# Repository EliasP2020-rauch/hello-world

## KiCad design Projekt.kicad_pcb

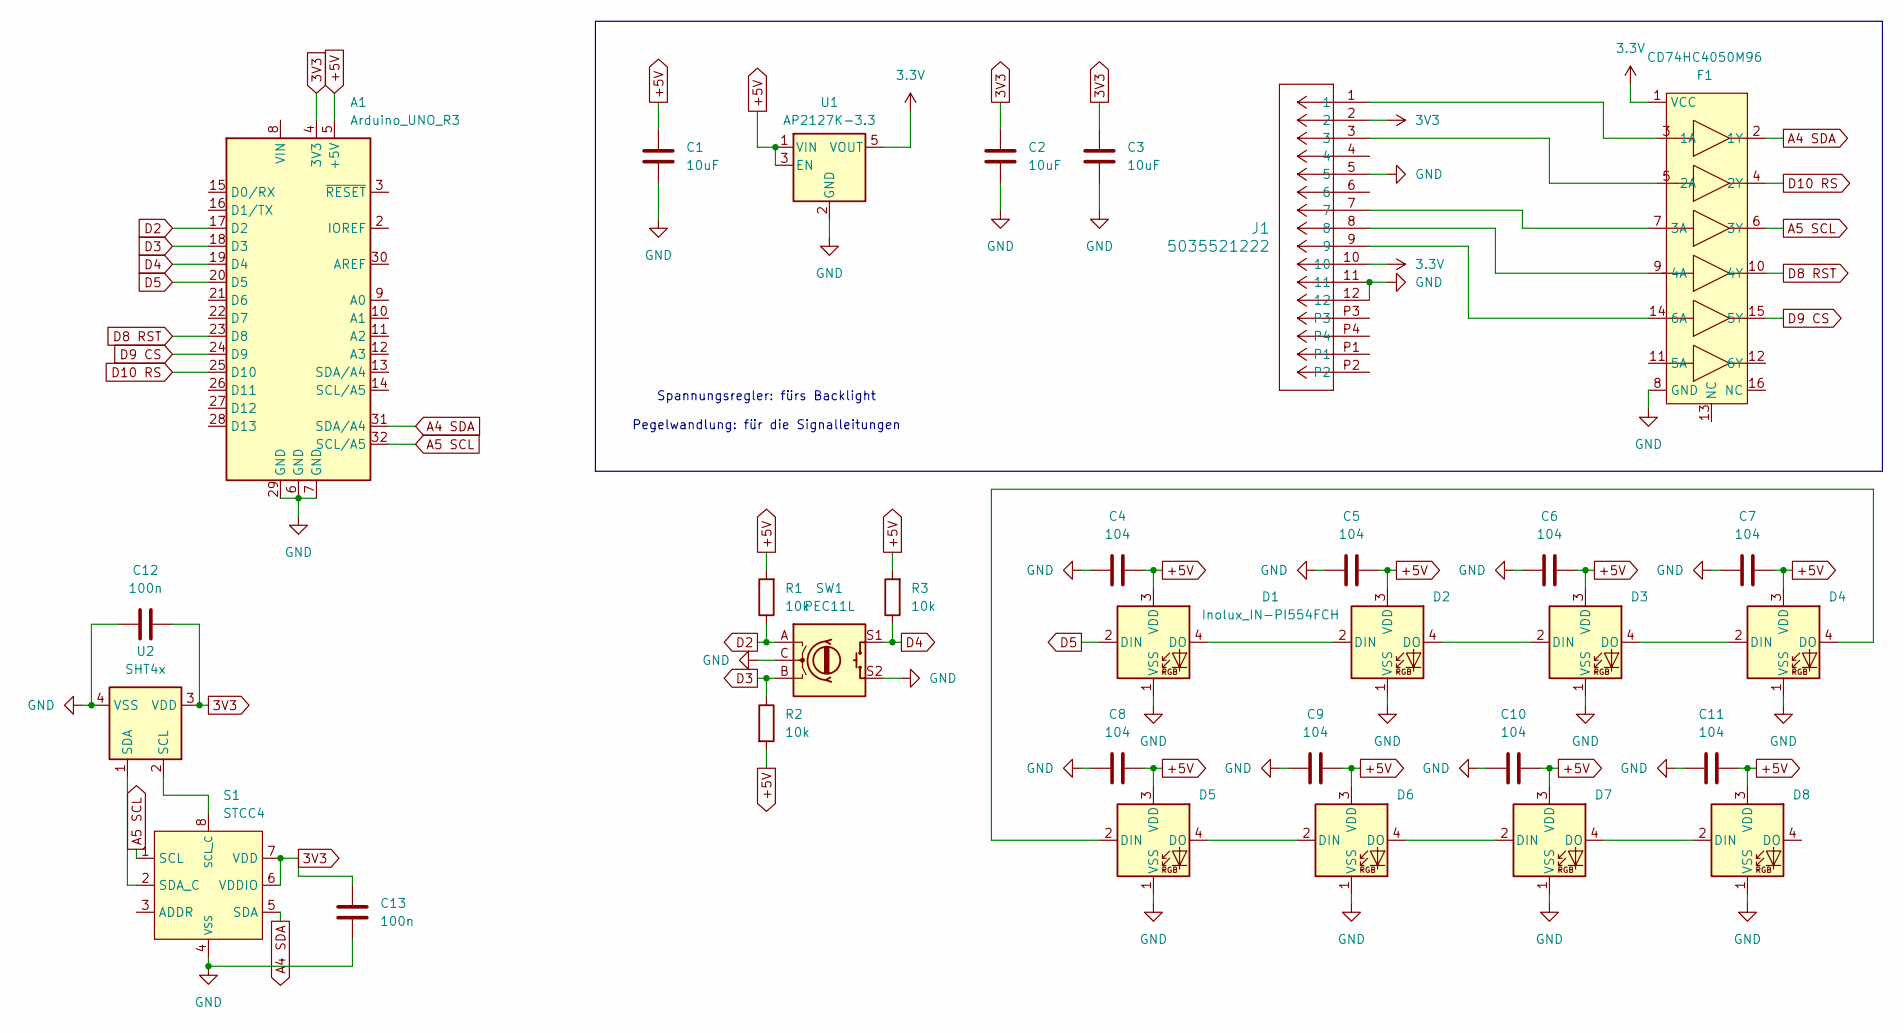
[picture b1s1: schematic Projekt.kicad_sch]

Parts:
A1: Arduino_UNO_R3
C1, C2, C3: 10uF; C_0805_2012Metric
C4, C5, C6, C7, C8, C9, C10, C11: 104; C_0402_1005Metric
C12, C13: 100n; C_0402_1005Metric
CD74HC4050M96: F1; CD74HC4050M96
D1: Inolux_IN-PI554FCH; LED_Inolux_IN-PI554FCH_PLCC4_5.0x5.0mm_P3.2mm
D2, D3, D4, D5, D6, D7, D8: LED_Inolux_IN-PI554FCH_PLCC4_5.0x5.0mm_P3.2mm
J1: 5035521222; 5035521222_D2.60mm_H0.70mm_P0.40mm
R1, R2, R3: 10k; R_0402_1005Metric
S1: STCC4
SW1: PEC11L
U1: AP2127K-3.3; SOT-23-5
U2: SHT4x; Sensirion_DFN-4_1.5x1.5mm_P0.8mm_SHT4x_NoCentralPad

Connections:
3.3V: CD74HC4050M96.1 (VCC), J1.10, U1.5 (VOUT)
3V3: A1.4 (3V3), C2.1, C3.1, C12.1, C13.1, J1.2, S1.6 (VDDIO), S1.7 (VDD), U2.3 (VDD)
+5V: A1.5 (+5V), C1.1, C4.1, C5.1, C6.1, C7.1, C8.1, C9.1, C10.1, C11.1, D1.3 (VDD), D2.3 (VDD), D3.3 (VDD), D4.3 (VDD), D5.3 (VDD), D6.3 (VDD), D7.3 (VDD), D8.3 (VDD), R1.2, R2.2, R3.2, U1.1 (VIN), U1.3 (EN)
A4 SDA: A1.31 (SDA/A4), CD74HC4050M96.2 (1Y), S1.5 (SDA)
A5 SCL: A1.32 (SCL/A5), CD74HC4050M96.6 (3Y), S1.1 (SCL)
D2: A1.17 (D2), R1.1, SW1.A
D3: A1.18 (D3), R2.1, SW1.B
D4: A1.19 (D4), R3.1, SW1.S1
D5: A1.20 (D5), D1.2 (DIN)
D8 RST: A1.23 (D8), CD74HC4050M96.10 (4Y)
D9 CS: A1.24 (D9), CD74HC4050M96.15 (5Y)
D10 RS: A1.25 (D10), CD74HC4050M96.4 (2Y)
GND: A1.6 (GND), A1.7 (GND), A1.29 (GND), C1.2, C2.2, C3.2, C4.2, C5.2, C6.2, C7.2, C8.2, C9.2, C10.2, C11.2, C12.2, C13.2, CD74HC4050M96.8 (GND), D1.1 (VSS), D2.1 (VSS), D3.1 (VSS), D4.1 (VSS), D5.1 (VSS), D6.1 (VSS), D7.1 (VSS), D8.1 (VSS), J1.5, J1.11, J1.12, S1.4 (VSS), SW1.C, SW1.S2, U1.2 (GND), U2.4 (VSS)
unnamed: CD74HC4050M96.3 (1A), J1.1
unnamed: CD74HC4050M96.5 (2A), J1.3
unnamed: CD74HC4050M96.7 (3A), J1.7
unnamed: CD74HC4050M96.9 (4A), J1.8
unnamed: CD74HC4050M96.14 (6A), J1.9
unnamed: D1.4 (DO), D2.2 (DIN)
unnamed: D2.4 (DO), D3.2 (DIN)
unnamed: D3.4 (DO), D4.2 (DIN)
unnamed: D4.4 (DO), D5.2 (DIN)
unnamed: D5.4 (DO), D6.2 (DIN)
unnamed: D6.4 (DO), D7.2 (DIN)
unnamed: D7.4 (DO), D8.2 (DIN)
unnamed: S1.8 (SCL_C), U2.2 (SCL)
unnamed: S1.2 (SDA_C), U2.1 (SDA)

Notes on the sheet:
Spannungsregler: fürs Backlight Pegelwandlung: für die Signalleitungen

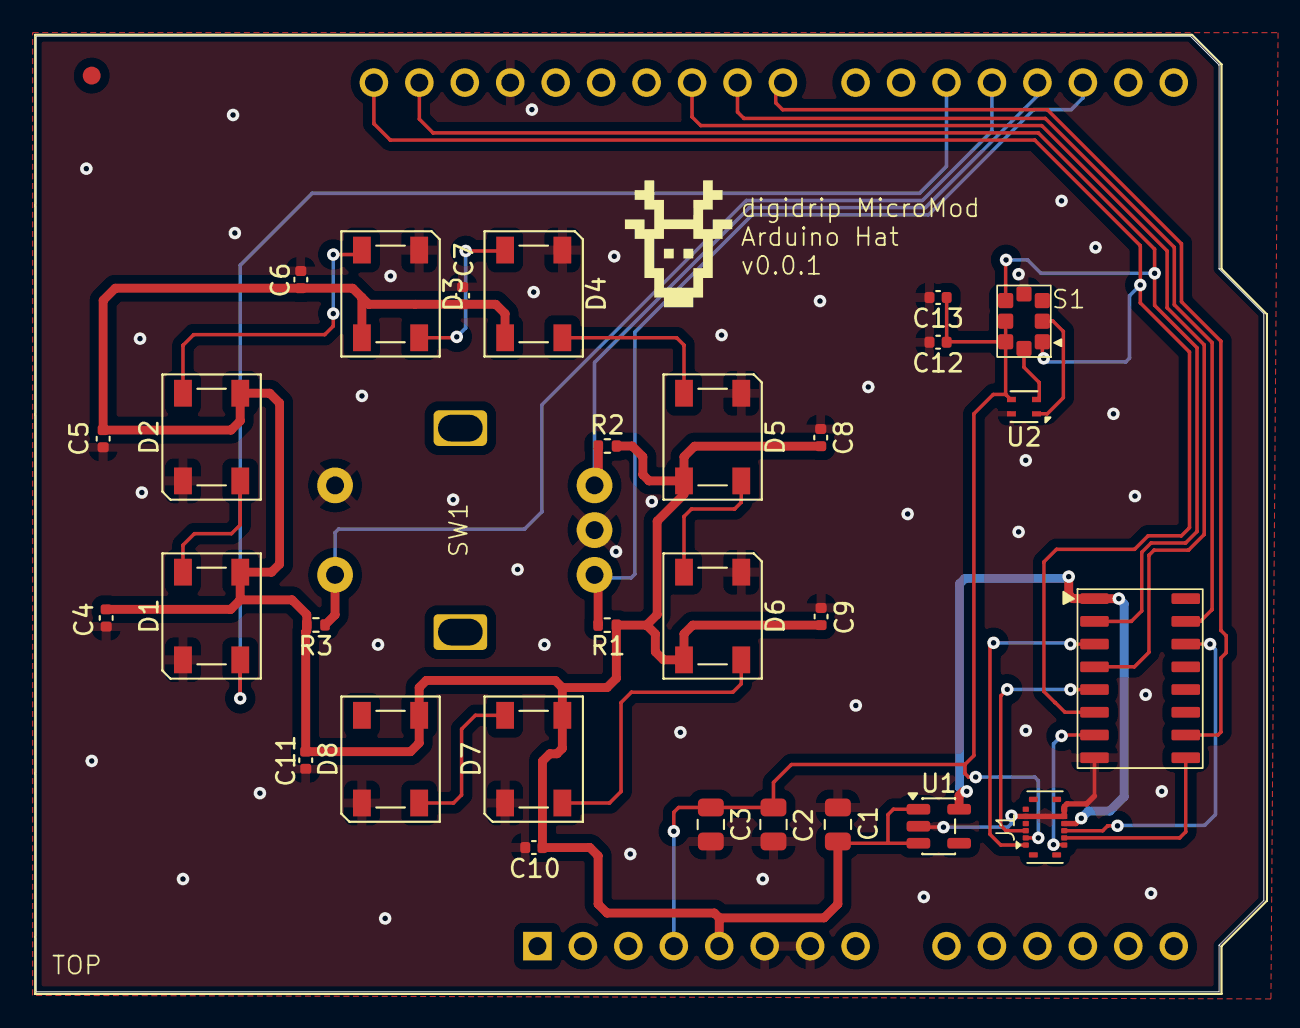
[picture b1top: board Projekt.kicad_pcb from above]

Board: 2 copper layers, 68.6 x 53.4 mm, 31 parts (0 on the bottom side), 27 nets.
